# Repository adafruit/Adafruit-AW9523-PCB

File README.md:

## Adafruit AW9523 GPIO Expander and LED Driver PCB

<a href="http://www.adafruit.com/products/4886"><br/>
Click here to purchase one from the Adafruit shop</a>

PCB files for the Adafruit AW9523 GPIO Expander and LED Driver. 

Format is EagleCAD schematic and board layout
* https://www.adafruit.com/product/4886

### Description

Expand your project possibilities, with the Adafruit AW9523 GPIO Expander and LED Driver Breakout - a cute and powerful I2C expander with a lot of tricks up it's sleeve.

GPIO expanders work like this: you have a board with some number of GPIO but not enough for your project - maybe you need more buttons or LEDs. You could upgrade to a board with massive number of GPIO like the Grand Central, or you could pop on one of these boards. Connect it over I2C and then you can send/receive I2C commands to control the GPIO pins to write and read them. It's going to be slower than direct GPIO access, but maybe that doesn't matter if it takes a millisecond instead of a microsecond. You only need the two I2C pins, and you can even share the I2C port with other sensors and devices. Heck, you can even add more expanders for massive I/O control!

The AW9523 is a twist on the common I2C expander:

* First up, its very affordable - who doesn't love that?
* It has 16 I/O pins, that'll double most boards' pin count
* Four I2C address options, so you can connect 4 expanders to one bus
* Each pin can be an input or an output
* IRQ output can alert you when input pins change value
* This chip does not support internal pull-ups or pull-downs, you will need to add an external resistor if you need one
* However, it does have 8-bit linear constant-current LED dimming support so you can connect LEDs without resistors and have great looking dimming without PWM
* The first 8 pins can be configured as open drain (as a group)

The lack of internally-configurable pull's is a bit of a bummer, but we think the expander more than makes up for it with the constant-current LED drive. If you're using an expander to add lots of controllable LEDs, this board will make it very easy. Since its constant-current, you don't need resistors in line with each LED (although it won't hurt if you do): simply connect the LED anode to one of the many VIN pads, then connect the cathode to the GPIO pin.

Of course, you can control any buttons or other I/O with the pins - we just think this board is particularly suited to LED driving. There's also an interrupt output, you can enable the pin-change IRQ for any pins so you can be notified when its time to read the I/O states.

One oddity about this chip is the default I2C address determines the initial boot-state of the pins. Our libraries immediately soft-reset and configure all the pins to inputs and push-pull so you can expect the same behavior no matter what the I2C address is. However, we recommend you check the datasheet Table 1 to make sure this doesn't affect your hardware.

We've written both Arduino and CircuitPython/Python libraries for the AW9523, so you can get started whether you have an Arduino-compatible UNO or a Raspberry Pi 4 - or anything in between.

To get you going fast, we spun up a custom made PCB in the STEMMA QT form factor, making it easy to interface with. The STEMMA QT connectors on either side are compatible with the SparkFun Qwiic I2C connectors. This allows you to make solderless connections between your development board and the AW9523 or to chain it with a wide range of other sensors and accessories using a compatible cable. QT Cable is not included, but we have a variety in the shop.

### License

Adafruit invests time and resources providing this open source design, please support Adafruit and open-source hardware by purchasing products from [Adafruit](https://www.adafruit.com)!

Designed by Limor Fried/Ladyada for Adafruit Industries.

Creative Commons Attribution/Share-Alike, all text above must be included in any redistribution. 
See license.txt for additional details.

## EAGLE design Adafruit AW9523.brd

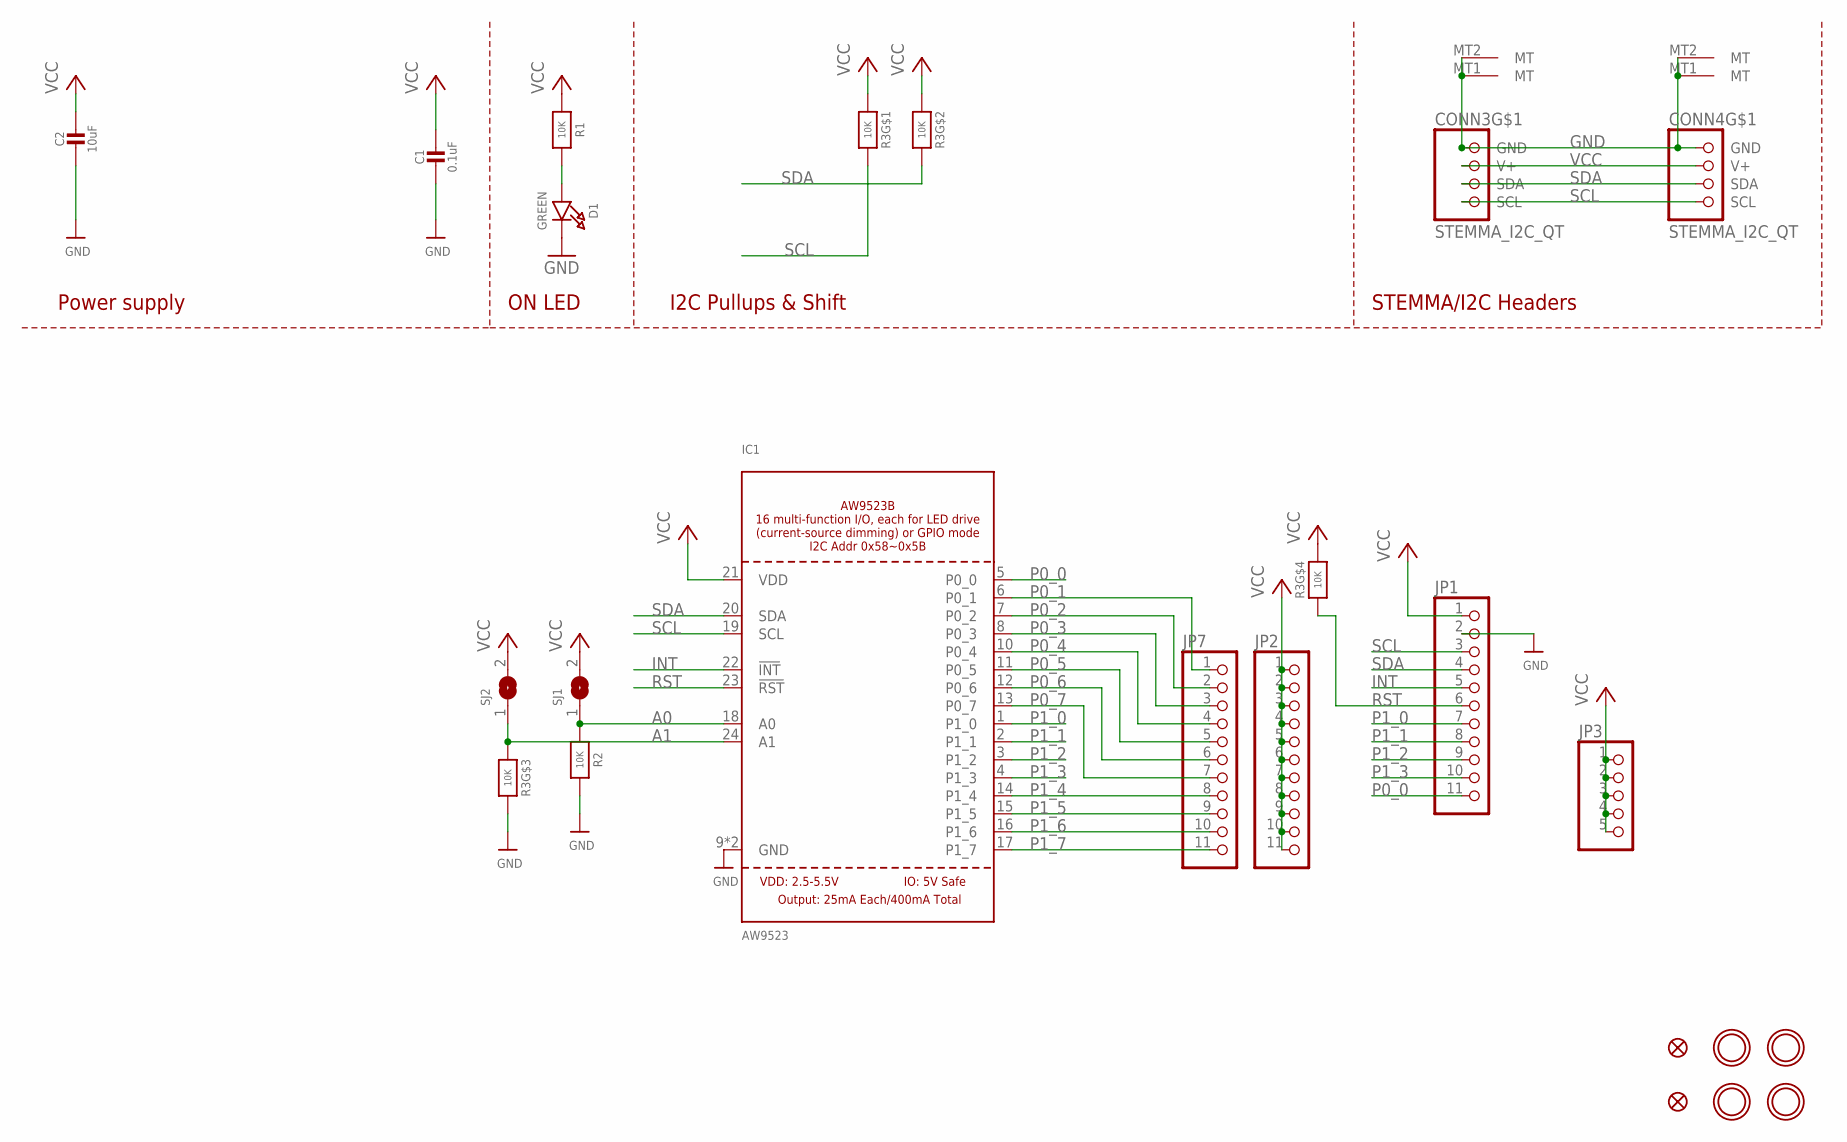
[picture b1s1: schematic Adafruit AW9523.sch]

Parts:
C1: 0.1uF; 0603-NO
C2: 10uF; 0805-NO
CONN3, CONN4: STEMMA_I2C_QT; JST_SH4
D1: GREEN; CHIPLED_0603_NOOUTLINE
FID3, FID4: FIDUCIAL_1MM
IC1: AW9523; QFN24_4MM_SMSC
JP1, JP2, JP7: HEADER-1X11; 1X11_ROUND
JP3: HEADER-1X5ROUND; 1X05_ROUND
R1, R2: 10K; 0603-NO
R3: 10K; RESPACK_4X0603
SJ1, SJ2: SOLDERJUMPER; SOLDERJUMPER_ARROW_NOPASTE
U$1, U$17, U$19, U$21: MOUNTINGHOLE2.5; MOUNTINGHOLE_2.5_PLATED

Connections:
A0: IC1.18 (A0), R2.1, SJ1.1
A1: IC1.24 (A1), R3.3 (1), SJ2.1
GND: C1.2, C2.2, CONN3.1 (GND), CONN3.MT1 (MT), CONN3.MT2 (MT), CONN4.1 (GND), CONN4.MT1 (MT), CONN4.MT2 (MT), D1.C, IC1.9 (GND), IC1.THERM (GND), JP1.2, R2.2, R3.6 (2)
INT: IC1.22 (!INT), JP1.5
unnamed: D1.A, R1.2
P0_0: IC1.5 (P0_0), JP1.11
P0_1: IC1.6 (P0_1), JP7.1
P0_2: IC1.7 (P0_2), JP7.2
P0_3: IC1.8 (P0_3), JP7.3
P0_4: IC1.10 (P0_4), JP7.4
P0_5: IC1.11 (P0_5), JP7.5
P0_6: IC1.12 (P0_6), JP7.6
P0_7: IC1.13 (P0_7), JP7.7
P1_0: IC1.1 (P1_0), JP1.7
P1_1: IC1.2 (P1_1), JP1.8
P1_2: IC1.3 (P1_2), JP1.9
P1_3: IC1.4 (P1_3), JP1.10
P1_4: IC1.14 (P1_4), JP7.8
P1_5: IC1.15 (P1_5), JP7.9
P1_6: IC1.16 (P1_6), JP7.10
P1_7: IC1.17 (P1_7), JP7.11
RST: IC1.23 (!RST), JP1.6, R3.4 (1)
SCL: CONN3.4 (SCL), CONN4.4 (SCL), IC1.19 (SCL), JP1.3, R3.8 (2)
SDA: CONN3.3 (SDA), CONN4.3 (SDA), IC1.20 (SDA), JP1.4, R3.7 (2)
VCC: C1.1, C2.1, CONN3.2 (V+), CONN4.2 (V+), IC1.21 (VDD), JP1.1, JP2.1, JP2.2, JP2.3, JP2.4, JP2.5, JP2.6, JP2.7, JP2.8, JP2.9, JP2.10, JP2.11, JP3.1, JP3.2, JP3.3, JP3.4, JP3.5, R1.1, R3.1, R3.2 (1), R3.5 (2), SJ1.2, SJ2.2

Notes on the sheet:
I2C Pullups & Shift
STEMMA/I2C Headers
ON LED
Power supply

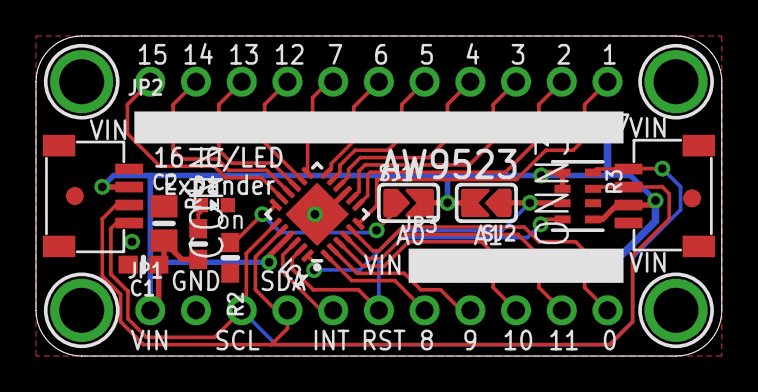
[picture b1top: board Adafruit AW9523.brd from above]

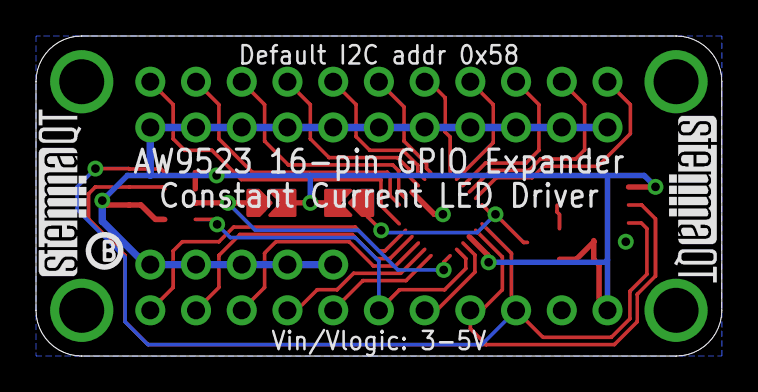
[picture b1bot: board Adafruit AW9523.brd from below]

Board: 2 copper layers, 38.1 x 17.8 mm, 24 parts (3 on the bottom side), 25 nets.

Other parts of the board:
U$2: PCBFEAT-REV-040
U$30, U$31: STEMMAQT

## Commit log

2021-02-09 Adding board files.

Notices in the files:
parts and their libraries:
microbuilder: This work is placed in the public domain, and may be freely used for commercial and non-commercial work with the following conditions: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
